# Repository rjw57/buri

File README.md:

# Operating System for my 6502 homebrew micro

This is a work-in-progress operation system for Buri, my homebrew 6502
microcomputer system. The hardware design can be found at
https://github.com/rjw57/buri-6502-hardware.

The OS is in the form of an 8K ROM image. Compilation of this software requires
[cc65](https://github.com/cc65/cc65). Assuming that cc65 is installed under
``$HOME/opt/cc65``, you can clone the source and make the image:

```console
$ git clone https://github.com/rjw57/buri-6502-os
$ cd buri-6502-os
$ CC65_DIR=$HOME/opt/cc65 make
```

## Syscalls

Syscalls are made via the `BRK` software-interrupt instruction. When a `BRK` is
issued, the OS uses the value of the `X` register to index an OS call. Return
values, if any, are stored in the `A` register.

## Calling conventions

The default throughout is for the M and X flags to be set (8-bit accumulator and
index) which allows for more compact immediate addressing instructions. Code
which enables a 16-bit register should take care to reset it before calling
other public code. Generally, "public" means code in a separate source file.
Functions should preserve the X and Y registers but are free to corrupt the A
register (or use it as a return value).

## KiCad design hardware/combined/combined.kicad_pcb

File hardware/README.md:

# Buri: a simple 6502-based computer

This is very much a work in progress repository. It contains schematics, notes,
etc. for a single-board 6502 computer I'm working on.

## Copying

See the [LICENSE](LICENSE.txt) file in the repository for copying information.

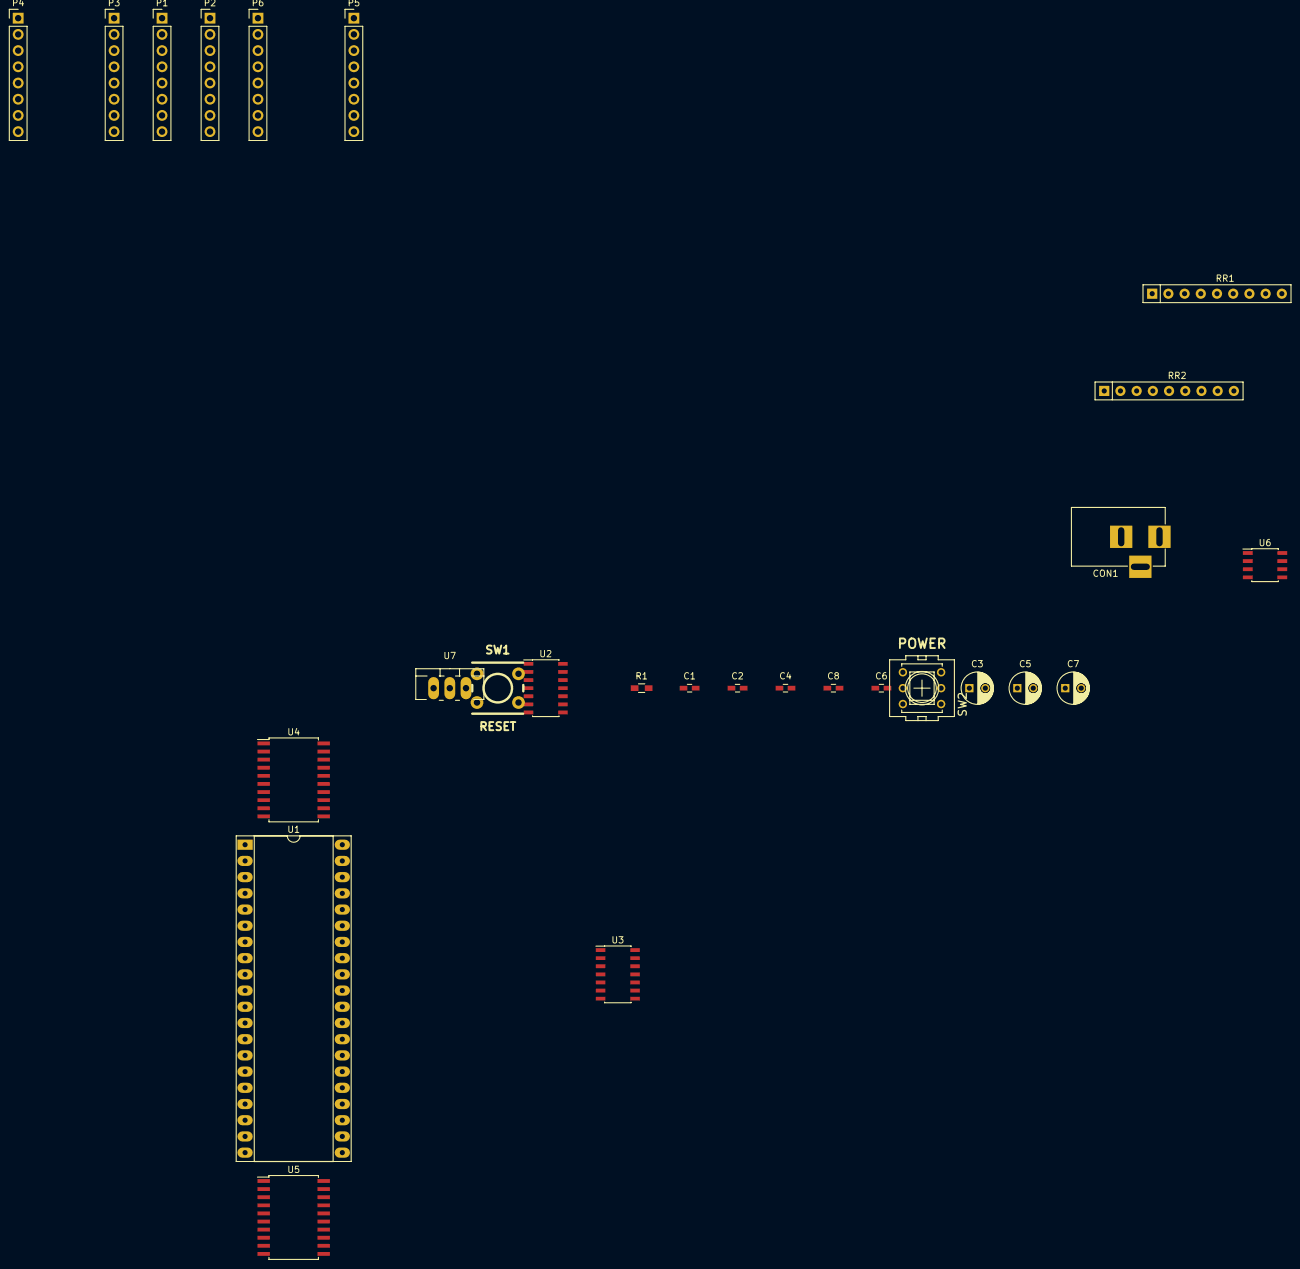
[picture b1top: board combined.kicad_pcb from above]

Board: 2 copper layers, 27 parts (0 on the bottom side), 60 nets, no tracks yet.

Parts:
C1, C2, C4, C6, C8: 100n; C_0603_HandSoldering
C3, C5, C7: 1µ; C_Radial_D5_L6_P2.5
CON1: POWER_IN; BARREL_JACK
P1: A0..A7; Pin_Header_Straight_1x08_Pitch2.54mm
P2: A8..A15; Pin_Header_Straight_1x08_Pitch2.54mm
P3: A16..A23; Pin_Header_Straight_1x08_Pitch2.54mm
P4: D0..D7; Pin_Header_Straight_1x08_Pitch2.54mm
P5: CTRL1; Pin_Header_Straight_1x08_Pitch2.54mm
P6: CTRL2; Pin_Header_Straight_1x08_Pitch2.54mm
R1: 330; R_0603_HandSoldering
RR1, RR2: RR8; Resistor_Array_SIP9
SW1: RESET; SW_M6_PTH
SW2: POWER; switch-misc-PVA2R
U1: W65C816; DIP-40_W15.24mm_Socket_LongPads
U2: 74HC04; SOIC-14_3.9x8.7mm_Pitch1.27mm
U3: 74HC00; SOIC-14_3.9x8.7mm_Pitch1.27mm
U4: 74HC245; SOIC-20W_7.5x12.8mm_Pitch1.27mm
U5: 74HC573; SOIC-20W_7.5x12.8mm_Pitch1.27mm
U6: TL7705A; SOIC-8_3.9x4.9mm_Pitch1.27mm
U7: 7805; TO-220_Neutral123_Vertical_LargePads

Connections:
+5V: C1.1, C7.1, C8.1, P6.1, P6.2, R1.1, RR2.1, U1.8, U2.14, U3.14, U4.20, U5.20, U6.7, U6.8, U7.3
/BE: P5.2, RR2.6, U1.36, U2.3, U3.2
/CPU/~ABORT: RR2.5, U1.3
/PHI2: P6.4, U1.37, U2.1, U3.1
/R/~W: P5.8, U1.34, U4.1
/RDY: P5.1, RR2.7, U1.2
/~IRQ: P5.7, RR2.3, U1.4
/~ML: P5.4, U1.5
/~NMI: P5.6, RR2.4, U1.6
/~RST: P6.5, RR2.2, U1.40, U6.5
/~VP: P5.3, U1.1
A0: P1.1, U1.9
A1: P1.2, U1.10
A2: P1.3, U1.11
A3: P1.4, U1.12
A4: P1.5, U1.13
A5: P1.6, U1.14
A6: P1.7, U1.15
A7: P1.8, U1.16
A8: P2.1, U1.17
A9: P2.2, U1.18
A10: P2.3, U1.19
A11: P2.4, U1.20
A12: P2.5, U1.22
A13: P2.6, U1.23
A14: P2.7, U1.24
A15: P2.8, U1.25
A16: P3.1, U5.19
A17: P3.2, U5.18
A18: P3.3, U5.17
A19: P3.4, U5.16
A20: P3.5, U5.15
A21: P3.6, U5.14
A22: P3.7, U5.13
A23: P3.8, U5.12
D0: P4.1, RR1.2, U4.2
D1: P4.2, RR1.3, U4.3
D2: P4.3, RR1.4, U4.4
D3: P4.4, RR1.5, U4.5
D4: P4.5, RR1.6, U4.6
D5: P4.6, RR1.7, U4.7
D6: P4.7, RR1.8, U4.8
D7: P4.8, RR1.9, U4.9
GND: C1.2, C2.2, C3.2, C4.2, C5.2, C6.2, C7.2, C8.2, CON1.2, P5.5, P6.6, P6.7, P6.8, RR1.1, SW1.1, U1.21, U2.7, U3.7, U4.10, U5.10, U6.4, U7.2
unnamed: C2.1, R1.2, SW1.2, U6.2
unnamed: C3.1, U6.3
unnamed: C4.1, U6.1
unnamed: C5.1, C6.1, SW2.1, SW2.4, U7.1
unnamed: CON1.1, SW2.2, SW2.5
unnamed: U1.26, U4.11, U5.9
unnamed: U1.27, U4.12, U5.8
unnamed: U1.28, U4.13, U5.7
unnamed: U1.29, U4.14, U5.6
unnamed: U1.30, U4.15, U5.5
unnamed: U1.31, U4.16, U5.4
unnamed: U1.32, U4.17, U5.3
unnamed: U1.33, U4.18, U5.2
unnamed: U2.2, U5.11
unnamed: U2.4, U5.1
unnamed: U3.3, U4.19

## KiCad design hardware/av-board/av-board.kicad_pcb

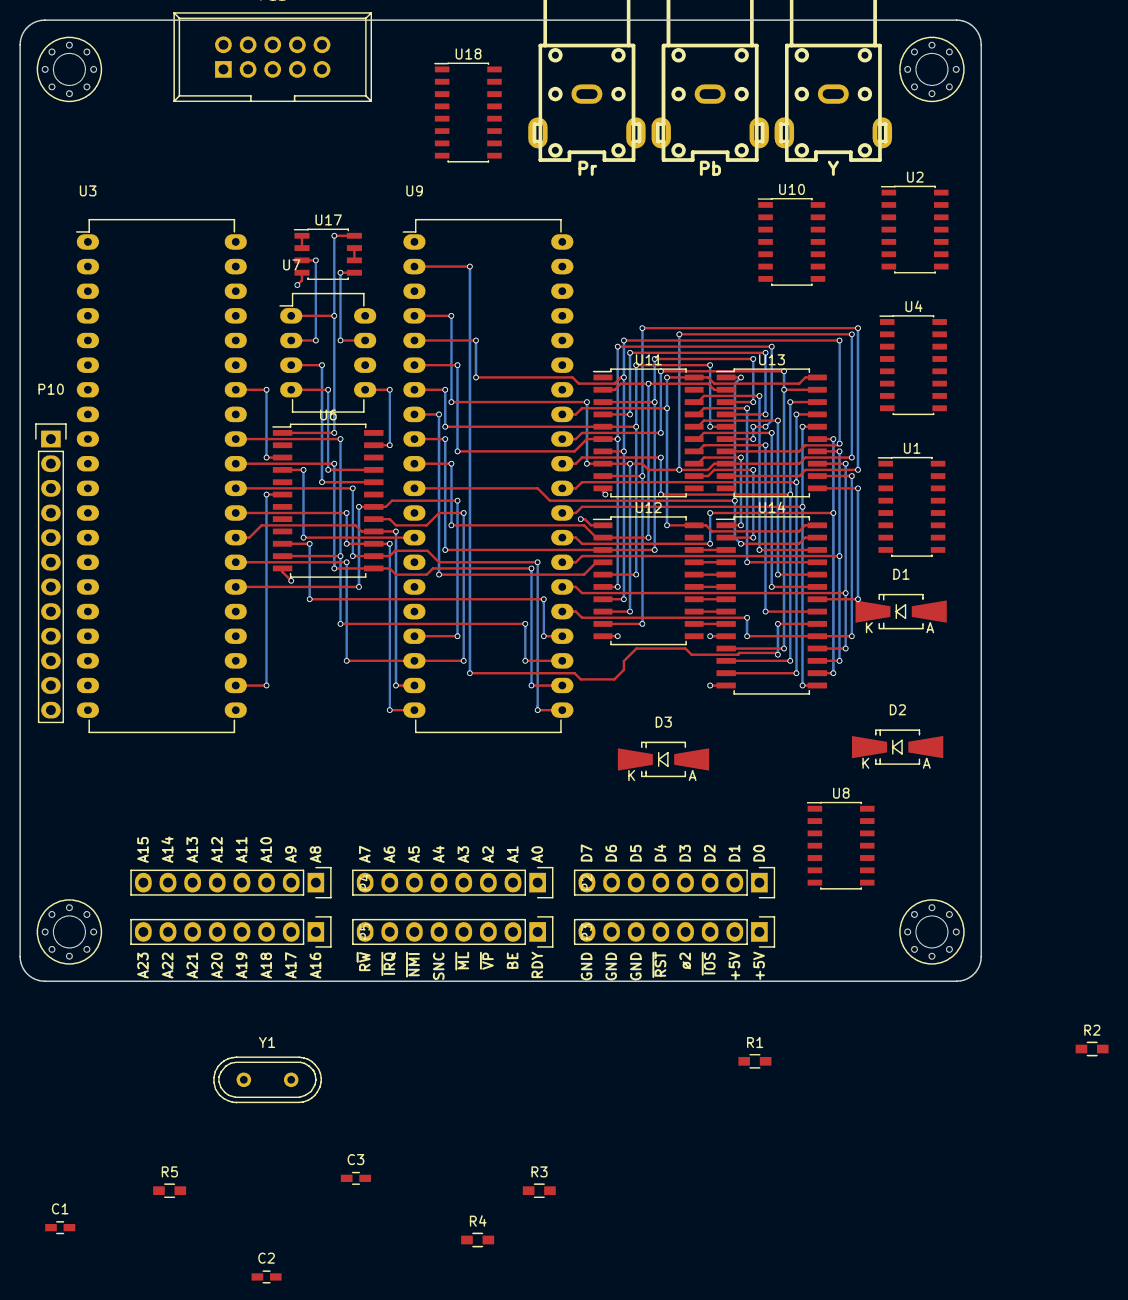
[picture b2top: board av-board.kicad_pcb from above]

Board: 2 copper layers, 99.1 x 99.1 mm, 42 parts (0 on the bottom side), 98 nets.

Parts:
C1, C2: 27pF; C_0603_HandSoldering
C3: 100n; C_0603_HandSoldering
D1, D2, D3: D_Small; SMA-SMB_Universal_Handsoldering
P1: D0..D7; Pin_Header_Straight_1x08
P2: A0..A7; Pin_Header_Straight_1x08
P3: CTRL1; Pin_Header_Straight_1x08
P4: A8..A15; Pin_Header_Straight_1x08
P5: A16..A23; Pin_Header_Straight_1x08
P6: CTRL2; Pin_Header_Straight_1x08
P7: Pr; rca_black
P8: Y; rca_black
P9: Pb; rca_black
P10: PARALLEL; Pin_Header_Straight_1x12
P11: KEYBOARD; IDC_Header_Straight_10pins
R1, R2, R3: 330; R_0603_HandSoldering
R4, R5: 1K; R_0603_HandSoldering
U1, U4, U18: 74HC138; SOIC-16_3.9x9.9mm_Pitch1.27mm
U2, U10: 74HC00; SOIC-14_3.9x8.7mm_Pitch1.27mm
U3: WD65C22; DIP-40_W15.24mm_LongPads
U6: YM3812; SOIC-24W_7.5x15.4mm_Pitch1.27mm
U7: YM3014; DIP-8_W7.62mm_LongPads
U8: 74HC04; SOIC-14_3.9x8.7mm_Pitch1.27mm
U9: TMS9929; DIP-40_W15.24mm_LongPads
U11, U12, U13: 74LS574; SOIC-20W_7.5x12.8mm_Pitch1.27mm
U14: CY62256; SOIC-28W_7.5x17.9mm_Pitch1.27mm
U17: TL072; SOIC-8_3.9x4.9mm_Pitch1.27mm
W1, W2, W3, W4: MOUNTING; M3_MOUNT
Y1: 21.48MHz; Crystal_HC49-U_Vertical

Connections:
+5V: P6.1, P6.2, P10.1, P11.2, U1.6, U1.16, U2.14, U3.20, U3.24, U4.16, U6.1, U7.1, U8.14, U9.33, U10.14, U11.20, U12.20, U13.20, U14.28, U17.8, U18.6, U18.16
/A0: P2.1, U3.38, U6.4, U9.13
/A1: P2.2, U3.37
/A2: P2.3, U3.36, U4.1
/A3: P2.4, U3.35, U4.2
/A4: P2.5, U1.1, U4.3
/A5: P2.6, U1.2, U4.6
/A6: P2.7, U1.3, U2.1
/A7: P2.8, U1.5, U2.2
/D0: P1.1, U3.33, U6.10, U9.24
/D1: P1.2, U3.32, U6.11, U9.23
/D2: P1.3, U3.31, U6.13, U9.22
/D3: P1.4, U3.30, U6.14, U9.21
/D4: P1.5, U3.29, U6.15, U9.20
/D5: P1.6, U3.28, U6.16, U9.19
/D6: P1.7, U3.27, U6.17, U9.18
/D7: P1.8, U3.26, U6.18, U9.17
/PHI2: P6.4, U3.25
/R/~W: P3.8, U3.22, U6.6, U10.12
/SPICLK: P11.3, U3.2
/SPIMISO: P11.1, U3.9
/SPIMOSI: P11.4, U3.3
/Sound/OUT: U17.1, U17.2
/Video/COL: U8.8, U12.11
/Video/SEL: U10.1, U10.13
/Video/VD0: U9.32, U13.19, U14.11
/Video/VD1: U9.31, U13.18, U14.12
/Video/VD2: U9.30, U13.17, U14.13
/Video/VD3: U9.29, U13.16, U14.15
/Video/VD4: U9.28, U13.15, U14.16
/Video/VD5: U9.27, U13.14, U14.17
/Video/VD6: U9.26, U13.13, U14.18
/Video/VD7: U9.25, U13.12, U14.19
/Video/VR/~W: U9.11, U13.1, U14.27
/Video/WR: U13.11, U14.22
/Video/~CAS: U9.2, U14.20
/Video/~CSR: U9.15, U10.11
/Video/~CSW: U9.14, U10.3
/W/~R: U6.5, U10.2
/~IOPAGE: P6.3, U1.4, U4.4
/~IRQ: D1.2, D2.2, D3.2, P3.7
/~RST: P6.5, U3.34, U6.3, U9.34
/~SNDS: U4.14, U6.7
/~SPIIRQ2: P11.9, U3.39
GND: C1.1, C2.1, C3.2, P6.6, P6.7, P6.8, P7.2, P8.2, P9.2, P10.12, P11.6, P11.8, P11.10, R1.2, R2.2, R3.2, U1.8, U2.7, U3.1, U4.8, U6.12, U7.6, U8.7, U9.12, U10.7, U11.1, U11.10, U12.1, U12.10, U13.10, U14.10, U14.14, U17.4, U18.4, U18.5, U18.8
unnamed: C1.2, R4.2, Y1.2
unnamed: C2.2, R5.1, Y1.1
unnamed: C3.1, U7.7, U17.5
unnamed: D1.1, U3.21
unnamed: D2.1, U6.2
unnamed: D3.1, U9.16
unnamed: P7.1, R1.1
unnamed: P8.1, R2.1
unnamed: P9.1, R3.1
unnamed: P10.2, U3.10
unnamed: P10.3, U3.11
unnamed: P10.4, U3.12
unnamed: P10.5, U3.13
unnamed: P10.6, U3.14
unnamed: P10.7, U3.15
unnamed: P10.8, U3.16
unnamed: P10.9, U3.17
unnamed: P10.10, U3.18
unnamed: P10.11, U3.19
unnamed: R4.1, R5.2
unnamed: U1.15, U3.23
unnamed: U2.3, U4.5
unnamed: U6.20, U7.3
unnamed: U6.21, U7.4
unnamed: U6.23, U7.5
unnamed: U8.9, U8.10
unnamed: U9.10, U11.2, U12.2, U13.2
unnamed: U9.9, U11.3, U12.3, U13.3
unnamed: U9.8, U11.4, U12.4, U13.4
unnamed: U9.7, U11.5, U12.5, U13.5
unnamed: U9.6, U11.6, U12.6, U13.6
unnamed: U9.5, U11.7, U12.7, U13.7
unnamed: U9.4, U11.8, U12.8, U13.8
unnamed: U9.3, U11.9, U12.9, U13.9
unnamed: U11.12, U14.2
unnamed: U11.13, U14.1
unnamed: U11.14, U14.21
unnamed: U11.15, U14.23
unnamed: U11.16, U14.24
unnamed: U11.17, U14.25
unnamed: U11.18, U14.26
unnamed: U12.12, U14.9
unnamed: U12.13, U14.8
unnamed: U12.14, U14.7
unnamed: U12.15, U14.6
unnamed: U12.16, U14.5
unnamed: U12.17, U14.4
unnamed: U12.18, U14.3
unnamed: U7.2, U17.3
unnamed: U7.8, U17.6, U17.7
unnamed: U3.4, U18.1
unnamed: U3.5, U18.2
unnamed: U3.6, U18.3

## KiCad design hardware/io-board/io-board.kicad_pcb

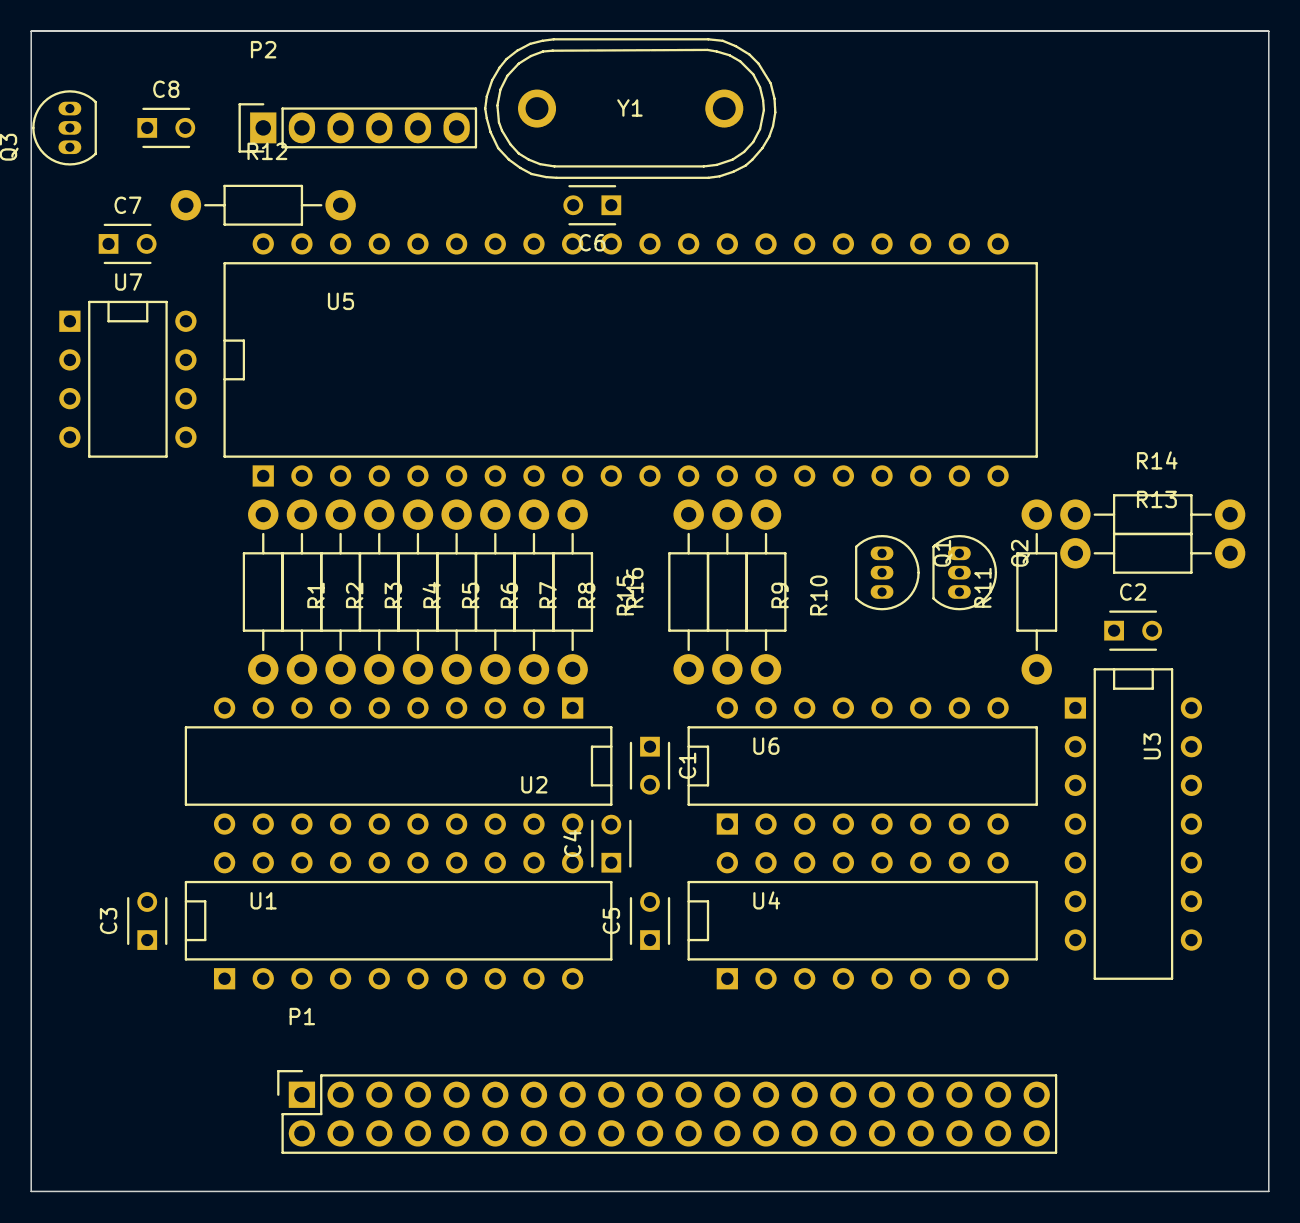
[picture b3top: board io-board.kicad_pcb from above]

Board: 2 copper layers, 81.3 x 76.2 mm, 37 parts (0 on the bottom side), 69 nets, no tracks yet.

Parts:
C1, C2, C3, C4, C5, C6, C7, C8: 10n; C_Disc_D3_P2.5
P1: BURI BUS; Socket_Strip_Straight_2x20
P2: SERIAL; Socket_Strip_Straight_1x06
Q1, Q2, Q3: BC546; TO-92_Inline_Narrow_Oval
R1, R2, R3, R4, R5, R6, R7, R8, R9, R10, R11, R12, R13, R14, R15, R16: 2K7; Resistor_Horizontal_RM10mm
U1: 74LS244; DIP-20__300
U2: 74HC245; DIP-20__300
U3: 7400; DIP-14__300
U4: 74LS138; DIP-16__300
U5: P8X32A-D40; DIP-40__600
U6: 4050; DIP-16__300
U7: 24C16; DIP-8__300
Y1: Crystal; Crystal_HC48-U_Vertical

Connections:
5V: C1.2, C2.2, C3.2, C4.2, C5.2, C6.2, C7.2, P1.17, P1.19, P1.21, P1.23, P2.5, R13.2, R14.2, R16.2, U1.20, U2.20, U3.14, U4.16, U5.12, U5.32, U6.1, U7.8
A0: P1.1, U1.2
A1: P1.3, U1.4
A2: P1.5, U1.6
A3: P1.7, U1.8
A4: P1.9, U1.17
A5: P1.11, U1.15
A6: P1.13, U1.13
A7: P1.15, U1.11
A8: P1.25, R9.2
A9: P1.27, R10.2
A10: P1.29, U4.3
A11: P1.31, U4.5
A12: P1.33, U4.2
A13: P1.35, U4.4
A14: P1.37, U4.1
A15: P1.39, U4.6
D0: P1.2, U2.11
D1: P1.4, U2.12
D2: P1.6, U2.13
D3: P1.8, U2.14
D4: P1.10, U2.15
D5: P1.12, U2.16
D6: P1.14, U2.17
D7: P1.16, U2.18
DA0: R1.1, U5.1
DA1: R2.1, U5.2
DA2: R3.1, U5.3
DA3: R4.1, U5.4
DA4: R5.1, U5.5
DA5: R6.1, U5.6
DA6: R7.1, U5.7
DA7: R8.1, U5.8
DA8: R9.1, U5.13
DA9: R10.1, U5.14
DEN/~AEN: R11.2, U3.4, U3.5, U3.9, U5.20
DTR: C8.2, P2.1
GND: C1.1, C2.1, C3.1, C4.1, C5.1, C6.1, C7.1, P1.20, P1.22, P2.6, Q1.3, Q2.3, Q3.3, R11.1, R15.1, U1.10, U2.10, U3.7, U4.8, U5.9, U5.10, U5.29, U6.8, U7.1, U7.2, U7.3, U7.4, U7.7
IRQ: Q2.2, U5.19
unnamed: C8.1, Q3.2, R15.2
unnamed: R12.1, U5.40
unnamed: U3.3, U3.10, U3.12
unnamed: U3.6, U3.13
unnamed: U5.30, Y1.2
unnamed: U5.31, Y1.1
P10: U5.15, U6.2
P11: U5.16, U6.4
P12: U5.17, U6.6
PHI2: P1.28, U6.5
R0: R1.2, U1.18, U2.9
R1: R2.2, U1.16, U2.8
R2: R3.2, U1.14, U2.7
R3: R4.2, U1.12, U2.6
R4: R5.2, U1.3, U2.5
R5: R6.2, U1.5, U2.4
R6: R7.2, U1.7, U2.3
R7: R8.2, U1.9, U2.2
R/~W: P1.26, U2.1, U6.7
RDY: P1.32, Q1.1, R13.1
RES: Q3.1, U5.11
RX: P2.2, U5.39
SCL: U5.37, U7.6
SDA: R16.1, U5.38, U7.5
TX: P2.3, R12.2
~AEN: U1.1, U1.19, U3.11
~CS: U3.1, U3.2, U4.7, U6.3
~DEN: U2.19, U3.8
~IRQ: P1.30, Q2.1, R14.1
~RDY: Q1.2, U5.18

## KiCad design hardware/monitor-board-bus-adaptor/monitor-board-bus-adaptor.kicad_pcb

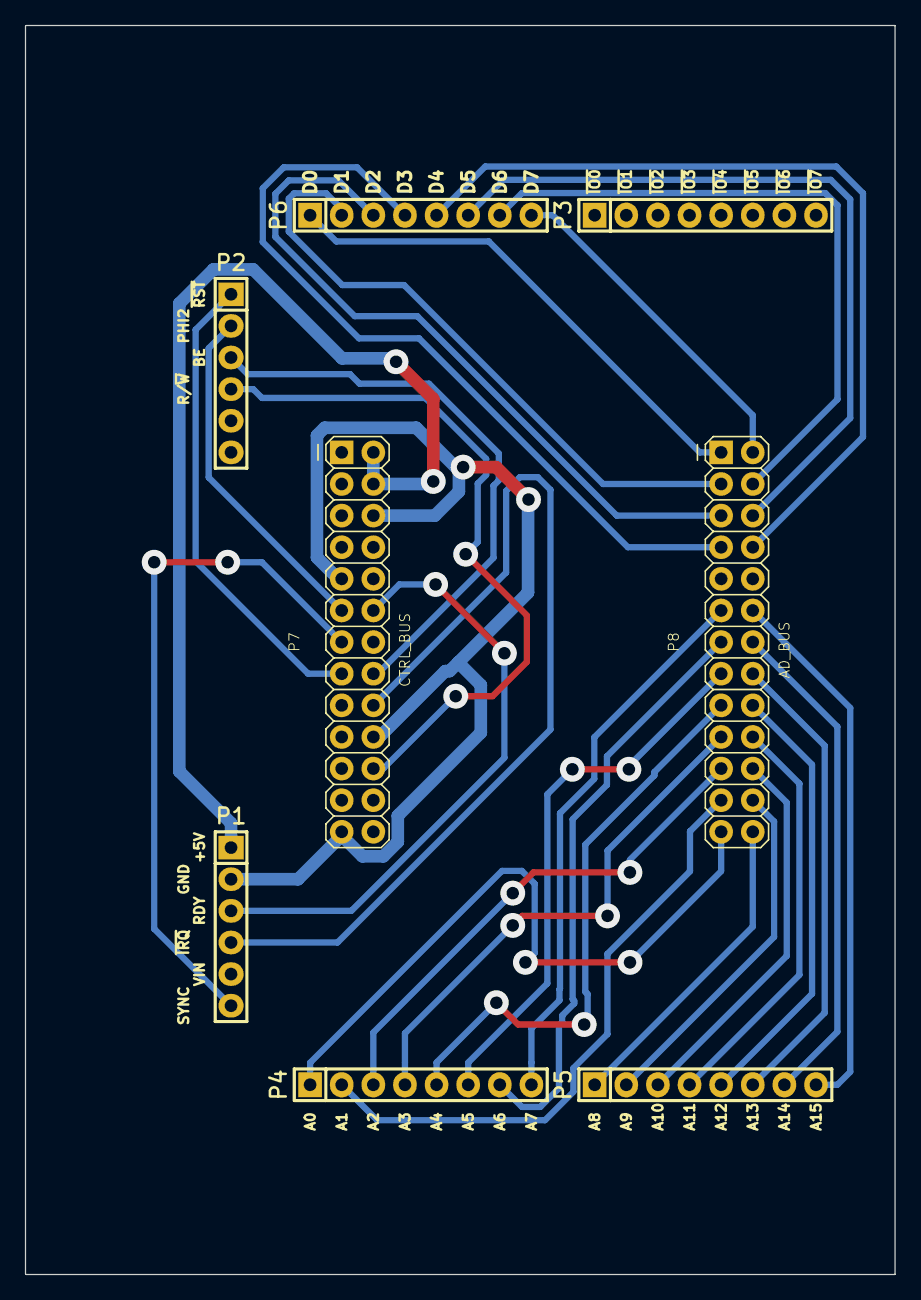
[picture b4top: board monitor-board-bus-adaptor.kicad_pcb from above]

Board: 2 copper layers, 69.8 x 100.3 mm, 8 parts (0 on the bottom side), 33 nets.

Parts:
P1: CTRL1; Pin_Header_Straight_1x06
P2: CTRL2; Pin_Header_Straight_1x06
P3: IO; Pin_Header_Straight_1x08
P4: ADDR1; Pin_Header_Straight_1x08
P5: ADDR2; Pin_Header_Straight_1x08
P6: DATA; Pin_Header_Straight_1x08
P7: CTRL_BUS; AB2_HDR_M13-2V
P8: AD_BUS; AB2_HDR_M13-2V

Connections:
+5V: P1.1, P7.2, P7.4
/A0: P4.1, P8.25
/A1: P4.2, P8.23
/A2: P4.3, P8.21
/A3: P4.4, P8.19
/A4: P4.5, P8.17
/A5: P4.6, P8.15
/A6: P4.7, P8.13
/A7: P4.8, P8.11
/A8: P5.1, P8.26
/A9: P5.2, P8.24
/A10: P5.3, P8.22
/A11: P5.4, P8.20
/A12: P5.5, P8.18
/A13: P5.6, P8.16
/A14: P5.7, P8.14
/A15: P5.8, P8.12
/D0: P6.1, P8.1
/D1: P6.2, P8.3
/D2: P6.3, P8.5
/D3: P6.4, P8.7
/D4: P6.5, P8.8
/D5: P6.6, P8.6
/D6: P6.7, P8.4
/D7: P6.8, P8.2
BE: P2.3, P7.16
GND: P1.2, P7.6, P7.9, P7.20, P7.25
PHI2: P2.2, P7.11
R/~W: P2.4, P7.22
RDY: P1.3, P7.12
SYNC: P1.6, P7.13
~IRQ: P1.4, P7.18
~RST: P2.1, P7.15

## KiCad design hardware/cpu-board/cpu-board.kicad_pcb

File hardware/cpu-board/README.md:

# Búri CPU board

This board contains the CPU, RAM and ROM along with a UART. It is the smallest
"standalone" computer which is of actual use within the Búri system.

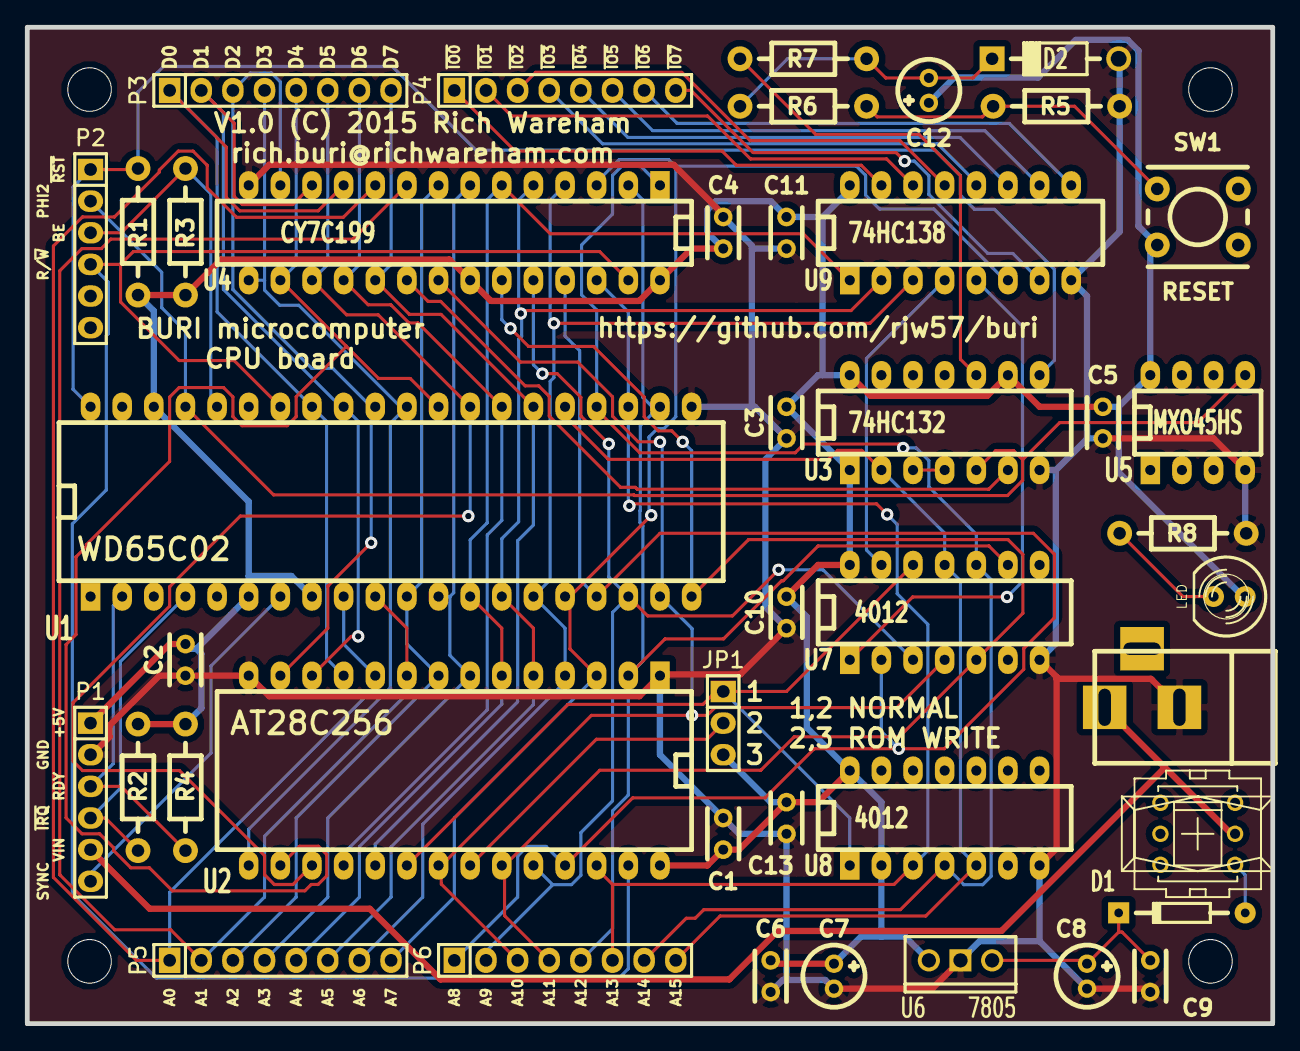
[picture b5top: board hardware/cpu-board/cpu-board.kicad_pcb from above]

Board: 2 copper layers, 100.0 x 80.0 mm, 44 parts (0 on the bottom side), 54 nets.

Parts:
C1, C2, C3, C4, C5, C9, C10, C11, C13: 10nF; Capacitor4x3RM2.5
C6: 4.7uF; Capacitor4x3RM2.5
C7: 10nF; Elko_vert_DM5_RM2
C8, C12: 4.7uF; Elko_vert_DM5_RM2
CON1: BARREL_JACK
D1: 1N4001; Diode_DO-35_SOD27_Horizontal_RM10
D2: 1N4148; Diode_DO-41_SOD81_Horizontal_RM10
D3: LED; LED-5MM
JP1: ROM PROGRAMMABLE; Pin_Header_Straight_1x03
Outl: EuroBoard_halb_Type-I_100mmX80mm_holes
P1: CTRL1; Socket_Strip_Straight_1x06
P2: CTRL2; Socket_Strip_Straight_1x06
P3: DATA; Socket_Strip_Straight_1x08
P4: IO; Socket_Strip_Straight_1x08
P5: ADDR1; Socket_Strip_Straight_1x08
P6: ADDR2; Socket_Strip_Straight_1x08
R1, R2, R3, R4, R6, R7: 10K; Resistor_Horizontal_RM10mm
R5: 47K; Resistor_Horizontal_RM10mm
R8: 330; Resistor_Horizontal_RM10mm
S1: PWR; switch-misc-PVA2F
SW1: RESET; SW_M6_PTH
U1: WD65C02; DIP-40__600_ELL
U2: AT28C256; DIP-28__600_ELL
U3: 74HC132; DIP-14__300_ELL
U4: CY7C199; DIP-28__300_ELL
U5: MXO45HS; DIP-8__300_ELL
U6: 7805; LM78XXV
U7, U8: 4012; DIP-14__300_ELL
U9: 74HC138; DIP-16__300_ELL

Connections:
+5V: C1.1, C2.1, C3.1, C4.1, C5.1, C6.1, C7.1, C10.1, C11.1, C12.1, C13.1, D3.1, JP1.3, P1.1, R1.1, R2.1, R3.1, R4.1, SW1.2, U1.6, U1.8, U1.38, U2.28, U3.1, U3.9, U3.14, U4.22, U4.28, U5.8, U6.VO, U7.14, U8.2, U8.14, U9.16
/Address Decode/~ROMSEL: JP1.1, U2.20, U7.12, U8.1
/~RAMCE: U3.6, U4.20
/~ROMOE: JP1.2, U2.22
A0: P5.1, U1.9, U2.10, U4.10
A1: P5.2, U1.10, U2.9, U4.9
A2: P5.3, U1.11, U2.8, U4.8
A3: P5.4, U1.12, U2.7, U4.7
A4: P5.5, U1.13, U2.6, U4.6, U9.1
A5: P5.6, U1.14, U2.5, U4.5, U9.2
A6: P5.7, U1.15, U2.4, U4.4, U9.3
A7: P5.8, U1.16, U2.3, U4.3, U9.6
A8: P6.1, U1.17, U2.25, U4.25, U7.2
A9: P6.2, U1.18, U2.24, U4.24, U7.3
A10: P6.3, U1.19, U2.21, U4.21, U7.4
A11: P6.4, U1.20, U2.23, U4.23, U7.5
A12: P6.5, U1.22, U2.2, U4.2, U7.9
A13: P6.6, U1.23, U2.26, U4.26, U8.3
A14: P6.7, U1.24, U4.1, U7.10, U8.4
A15: P6.8, U1.25, U3.2, U7.11, U8.5
BE: P2.3, R3.2, U1.36
D0: P3.1, U1.33, U2.11, U4.11
D1: P3.2, U1.32, U2.12, U4.12
D2: P3.3, U1.31, U2.13, U4.13
D3: P3.4, U1.30, U2.15, U4.15
D4: P3.5, U1.29, U2.16, U4.16
D5: P3.6, U1.28, U2.17, U4.17
D6: P3.7, U1.27, U2.18, U4.18
D7: P3.8, U1.26, U2.19, U4.19
GND: C1.2, C2.2, C3.2, C4.2, C5.2, C6.2, C7.2, C8.2, C9.2, C10.2, C11.2, C13.2, CON1.2, D2.1, P1.2, R5.2, R8.2, U1.21, U2.1, U2.14, U3.7, U4.14, U5.4, U6.GND, U7.7, U8.7, U9.8
unnamed: C8.1, C9.1, D1.2, U6.VI
unnamed: C12.2, D2.2, R6.1, R7.2
unnamed: D1.1, S1.1
unnamed: D3.2, R8.1
unnamed: R5.1, R6.2, SW1.1
unnamed: R7.1, U3.10
unnamed: U3.3, U3.4
unnamed: U7.1, U9.5
unnamed: U7.13, U9.4
PHI2: P2.2, U1.37, U3.5, U5.5
R/~W: P2.4, U1.34, U2.27, U4.27
RDY: P1.3, R4.2, U1.2
SYNC: P1.6, U1.7
VIN: CON1.1, P1.5, S1.2
~IO0: P4.1, U9.15
~IO1: P4.2, U9.14
~IO2: P4.3, U9.13
~IO3: P4.4, U9.12
~IO4: P4.5, U9.11
~IO5: P4.6, U9.10
~IO6: P4.7, U9.9
~IO7: P4.8, U9.7
~IRQ: P1.4, R2.2, U1.4
~RST: P2.1, R1.2, U1.40, U3.8

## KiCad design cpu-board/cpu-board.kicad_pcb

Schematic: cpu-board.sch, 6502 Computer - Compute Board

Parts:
C1, C2, C3, C4, C5, C9, C10, C11: 10nF
C6: 100nF
C7: 100uF
JP1: ROM PROGRAMMABLE
P1: DATA
P2: ADDR1
P3: ADDR2
P4: CTRL1
P5: CTRL2
P6: PWR
R1, R2, R3, R4: 3.3K
U1: WD65C02
U2: AT28C256
U3: MXO45HS
U4: 74HC132
U5: CY7C199
U9: 7805

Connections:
+5V: C1.1, C2.1, C3.1, C4.1, C5.1, C6.1, C7.1, C9.1, C10.1, C11.1, JP1.3, P4.1, R1.1, R2.1, R3.1, R4.1, U1.6 (~NMI), U1.8 (VCC), U1.38 (~SO), U2.28 (VCC), U3.8 (VCC), U4.1, U4.14 (VCC), U5.22 (OE), U5.28 (VCC), U9.VO; also elsewhere on the board
/Address Decode/~ROMSEL: JP1.1, U2.20 (CE); also elsewhere on the board
/D0: P1.1, U1.33 (D0), U2.11 (D0), U5.11 (D0)
/D1: P1.2, U1.32 (D1), U2.12 (D1), U5.12 (D1)
/D2: P1.3, U1.31 (D2), U2.13 (D2), U5.13 (D2)
/D3: P1.4, U1.30 (D3), U2.15 (D3), U5.15 (D3)
/D4: P1.5, U1.29 (D4), U2.16 (D4), U5.16 (D4)
/D5: P1.6, U1.28 (D5), U2.17 (D5), U5.17 (D5)
/D6: P1.7, U1.27 (D6), U2.18 (D6), U5.18 (D6)
/D7: P1.8, U1.26 (D7), U2.19 (D7), U5.19 (D7)
/VIN: P4.3, P6.1; also elsewhere on the board
/~RAMCE: U4.6, U5.20 (CE)
/~ROMOE: JP1.2, U2.22 (OE)
A0: P2.1, U1.9 (A0), U2.10 (A0), U5.10 (A14)
A1: P2.2, U1.10 (A1), U2.9 (A1), U5.9 (A13)
A2: P2.3, U1.11 (A2), U2.8 (A2), U5.8 (A12)
A3: P2.4, U1.12 (A3), U2.7 (A3), U5.7 (A11)
A4: P2.5, U1.13 (A4), U2.6 (A4), U5.6 (A10); also elsewhere on the board
A5: P2.6, U1.14 (A5), U2.5 (A5), U5.5 (A9); also elsewhere on the board
A6: P2.7, U1.15 (A6), U2.4 (A6), U5.4 (A8); also elsewhere on the board
A7: P2.8, U1.16 (A7), U2.3 (A7), U5.3 (A7); also elsewhere on the board
A8: P3.1, U1.17 (A8), U2.25 (A8), U5.25 (A3); also elsewhere on the board
A9: P3.2, U1.18 (A9), U2.24 (A9), U5.24 (A2); also elsewhere on the board
A10: P3.3, U1.19 (A10), U2.21 (A10), U5.21 (A0); also elsewhere on the board
A11: P3.4, U1.20 (A11), U2.23 (A11), U5.23 (A1); also elsewhere on the board
A12: P3.5, U1.22 (A12), U2.2 (A12), U5.2 (A6); also elsewhere on the board
A13: P3.6, U1.23 (A13), U2.26 (A13), U5.26 (A4); also elsewhere on the board
A14: P3.7, U1.24 (A14), U5.1 (A5); also elsewhere on the board
A15: P3.8, U1.25 (A15), U4.2; also elsewhere on the board
BE: P5.3, R3.2, U1.36 (BE)
GND: C1.2, C2.2, C3.2, C4.2, C5.2, C6.2, C7.2, C9.2, C10.2, C11.2, P4.2, P6.2, U1.21 (GND), U2.1 (A14), U2.14 (GND), U3.4 (GND), U4.7 (GND), U5.14 (GND), U9.GND; also elsewhere on the board
unnamed 40: U9.VI; also elsewhere on the board
unnamed: U4.3, U4.4
PHI2: P5.2, U1.37 (PHI0), U3.5 (CLK), U4.5
RDY: P4.6, R4.2, U1.2 (RDY)
SYNC: P4.4, U1.7 (SYNC)
~IRQ: P4.5, R2.2, U1.4 (~IRQ)
~RST: P5.1, R1.2, U1.40 (~RESET); also elsewhere on the board

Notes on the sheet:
AT U1
AT U2
AT U3
AT U5
Processor
RAM
EEPROM
Clock generation
AT U4
AT P6
Take ~ROMOE~ high to program
AT U6
AT U7
AT U8

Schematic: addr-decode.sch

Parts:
U4, U7: 4012
U8: 74HC138

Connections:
+5V: U7.2, U7.14, U8.16; also elsewhere on the board
/Address Decode/~IO0: U8.15; also elsewhere on the board
/Address Decode/~IO1: U8.14; also elsewhere on the board
/Address Decode/~IO2: U8.13; also elsewhere on the board
/Address Decode/~IO3: U8.12; also elsewhere on the board
/Address Decode/~IO4: U8.11; also elsewhere on the board
/Address Decode/~IO5: U8.10; also elsewhere on the board
/Address Decode/~IO6: U8.9; also elsewhere on the board
/Address Decode/~IO7: U8.7; also elsewhere on the board
/Address Decode/~ROMSEL: U7.1; also elsewhere on the board
A4: U8.1; also elsewhere on the board
A5: U8.2; also elsewhere on the board
A6: U8.3; also elsewhere on the board
A7: U8.6; also elsewhere on the board
A13: U7.3; also elsewhere on the board
A14: U7.4; also elsewhere on the board
A15: U7.5; also elsewhere on the board
GND: U7.7, U8.8; also elsewhere on the board
unnamed 44: U8.5; also elsewhere on the board
unnamed 45: U8.4; also elsewhere on the board

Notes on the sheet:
MEMORY MAP RAM: $0000-$7FFF (32K) ROM: $E000-$FFFF (8K) IO0..IO7: 8x16 byte regions starting at $DF80

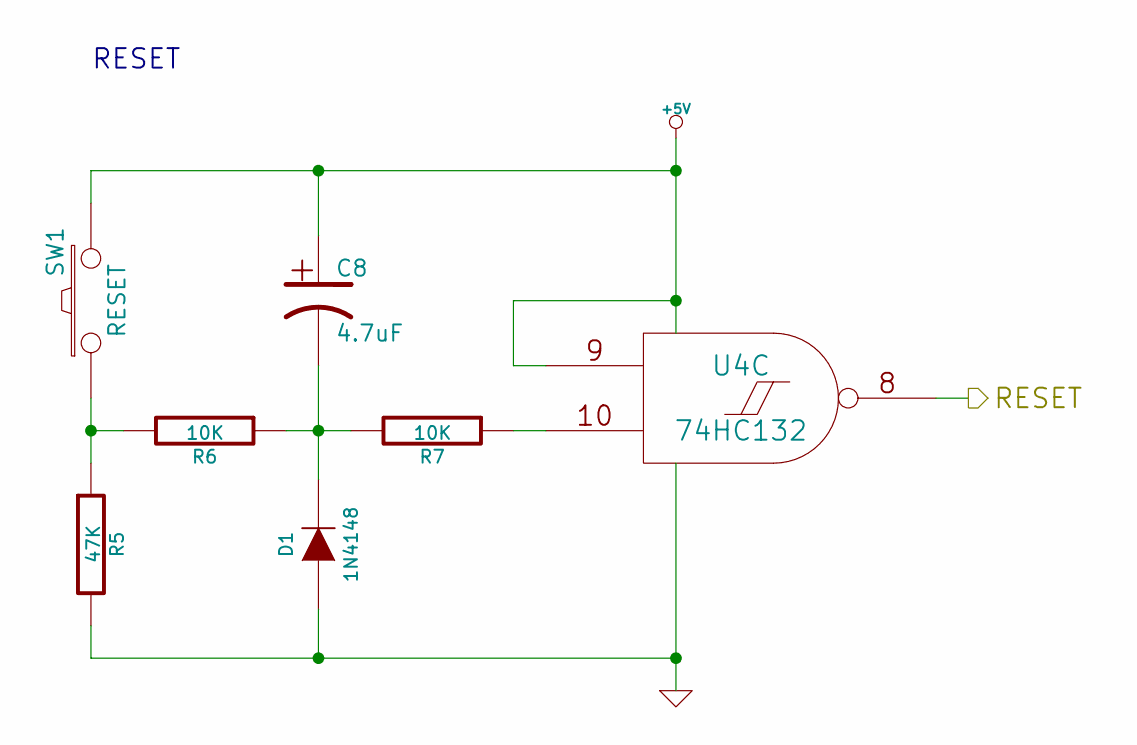
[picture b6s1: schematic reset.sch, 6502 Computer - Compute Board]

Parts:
C8: 4.7uF
D1: 1N4148
R5: 47K
R6, R7: 10K
SW1: RESET
U4: 74HC132

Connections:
+5V: C8.1, SW1.2, U4.9, U4.14 (VCC); also elsewhere on the board
GND: D1.1 (A), R5.2, U4.7 (GND); also elsewhere on the board
unnamed: C8.2, D1.2 (K), R6.1, R7.2
unnamed: R5.1, R6.2, SW1.1
unnamed: R7.1, U4.10
~RST: U4.8; also elsewhere on the board

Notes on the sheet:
RESET

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
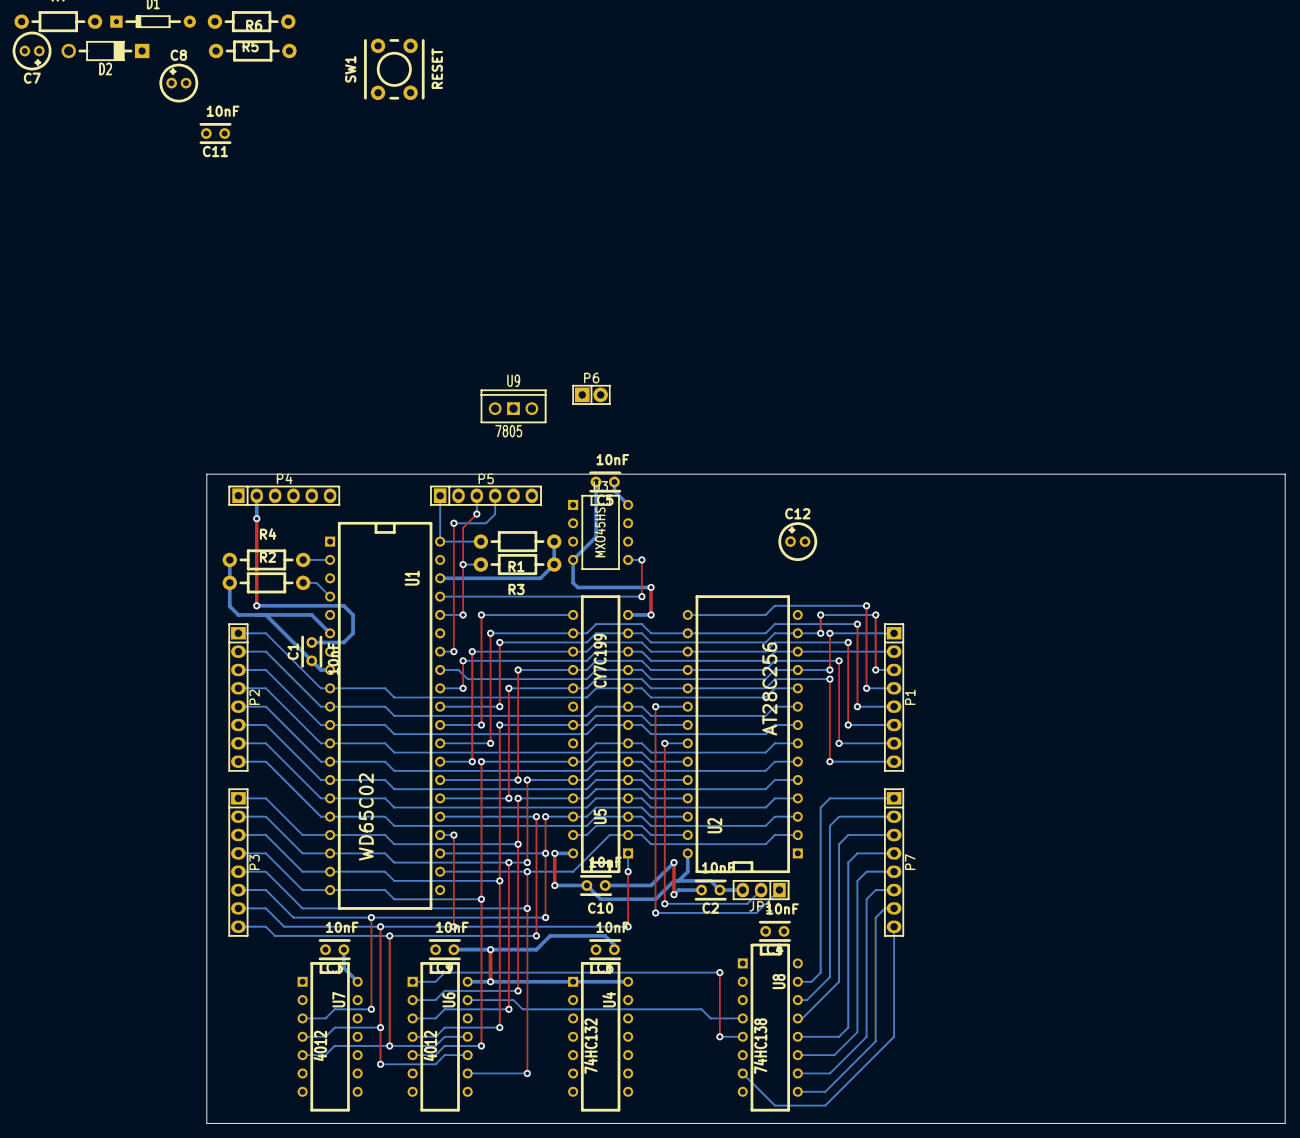
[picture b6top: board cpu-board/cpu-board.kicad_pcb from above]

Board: 2 copper layers, 149.4 x 89.9 mm, 39 parts (0 on the bottom side), 52 nets.

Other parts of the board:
C12: 4.7uF; Elko_vert_DM5_RM2
D2: 1N4001; Diode_DO-41_SOD81_Horizontal_RM10
P7: IO; Socket_Strip_Straight_1x08
U6: 4012; DIP-14__300

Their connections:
+5V: U6.14; also elsewhere on the board
/Address Decode/~IO0: P7.1; also elsewhere on the board
/Address Decode/~IO1: P7.2; also elsewhere on the board
/Address Decode/~IO2: P7.3; also elsewhere on the board
/Address Decode/~IO3: P7.4; also elsewhere on the board
/Address Decode/~IO4: P7.5; also elsewhere on the board
/Address Decode/~IO5: P7.6; also elsewhere on the board
/Address Decode/~IO6: P7.7; also elsewhere on the board
/Address Decode/~IO7: P7.8; also elsewhere on the board
/Address Decode/~ROMSEL: U6.12; also elsewhere on the board
/VIN: D2.1; also elsewhere on the board
A8: U6.2; also elsewhere on the board
A9: U6.3; also elsewhere on the board
A10: U6.4; also elsewhere on the board
A11: U6.5; also elsewhere on the board
A12: U6.9; also elsewhere on the board
A14: U6.10; also elsewhere on the board
A15: U6.11; also elsewhere on the board
GND: C12.2, U6.7; also elsewhere on the board
unnamed 40: C12.1, D2.2; also elsewhere on the board
unnamed 44: U6.1; also elsewhere on the board
unnamed 45: U6.13; also elsewhere on the board

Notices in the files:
hardware/cpu-board/cpu-board.kicad_pcb:
V1.0 (C) 2015 Rich Wareham
